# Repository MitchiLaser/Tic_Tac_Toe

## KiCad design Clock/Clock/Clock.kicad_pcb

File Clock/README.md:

# Clock
Ein einfacher Workshop bei dem Kinder eine binäre uhr löten und programmieren können

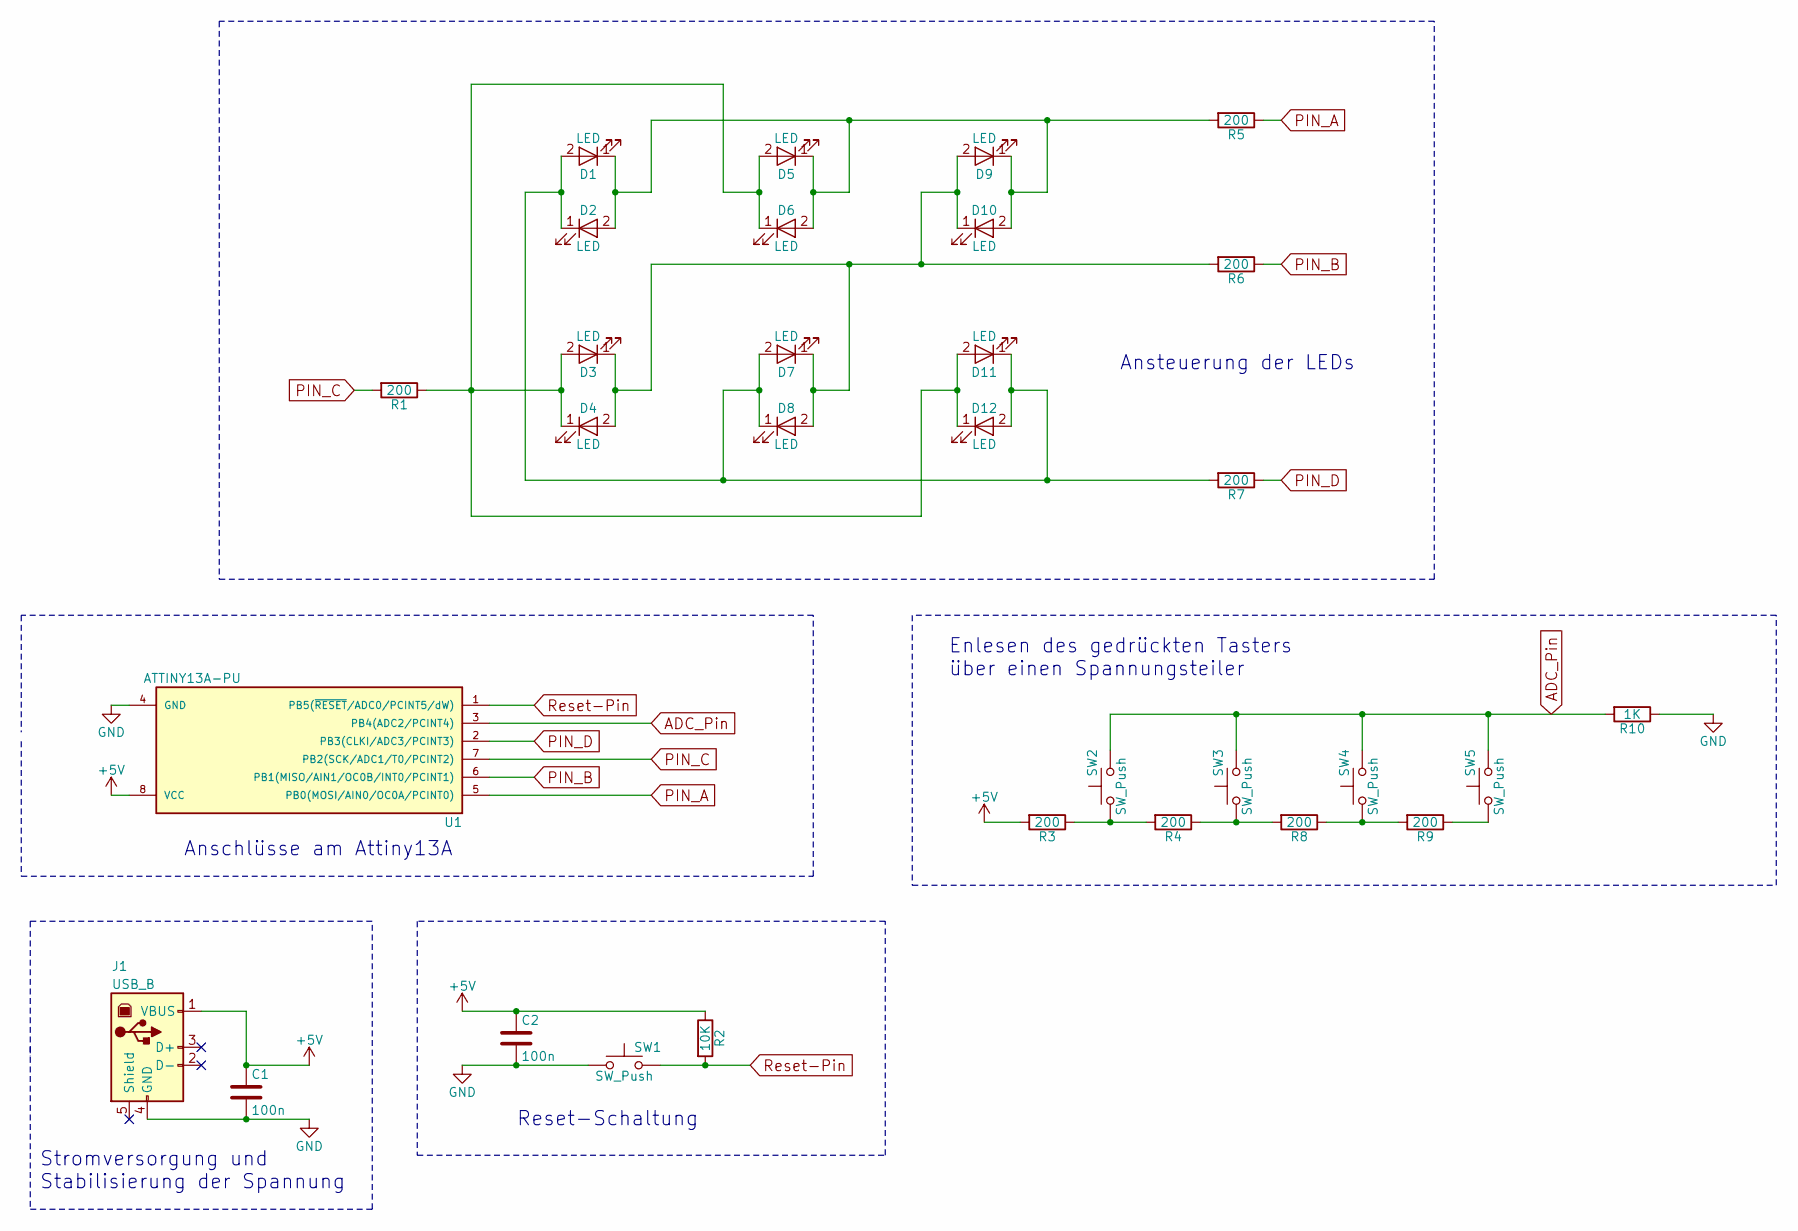
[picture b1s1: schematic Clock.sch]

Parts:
C1, C2: 100n; CP_Radial_Tantal_D5.0mm_P5.00mm
D1, D2, D3, D4, D5, D6, D7, D8, D9, D10, D11, D12: LED; LED_D5.0mm
J1: USB_B
R1, R3, R4, R5, R6, R7, R8, R9: 200; R_Axial_DIN0207_L6.3mm_D2.5mm_P10.16mm_Horizontal
R2: 10K; R_Axial_DIN0207_L6.3mm_D2.5mm_P10.16mm_Horizontal
R10: 1K; R_Axial_DIN0207_L6.3mm_D2.5mm_P10.16mm_Horizontal
SW1, SW2, SW3, SW4, SW5: SW_Push; SW_PUSH_6mm
U1: ATTINY13A-PU; DIP-8_W7.62mm

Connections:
+5V: C1.1, C2.1, J1.1 (VBUS), R2.1, R3.2, U1.8 (VCC)
ADC_Pin: R10.2, SW2.2, SW3.2, SW4.2, SW5.2, U1.3 (PB4(ADC2/PCINT4))
GND: C1.2, C2.2, J1.4 (GND), R10.1, SW1.1, U1.4 (GND)
unnamed: D1.1 (K), D2.2 (A), D5.1 (K), D6.2 (A), D9.1 (K), D10.2 (A), R5.2
unnamed: D1.2 (A), D2.1 (K), D7.2 (A), D8.1 (K), D11.1 (K), D12.2 (A), R7.2
unnamed: D3.1 (K), D4.2 (A), D7.1 (K), D8.2 (A), D9.2 (A), D10.1 (K), R6.2
unnamed: D3.2 (A), D4.1 (K), D5.2 (A), D6.1 (K), D11.2 (A), D12.1 (K), R1.1
unnamed: R3.1, R4.2, SW2.1
unnamed: R4.1, R8.2, SW3.1
unnamed: R8.1, R9.2, SW4.1
unnamed: R9.1, SW5.1
PIN_A: R5.1, U1.5 (PB0(MOSI/AIN0/OC0A/PCINT0))
PIN_B: R6.1, U1.6 (PB1(MISO/AIN1/OC0B/INT0/PCINT1))
PIN_C: R1.2, U1.7 (PB2(SCK/ADC1/T0/PCINT2))
PIN_D: R7.1, U1.2 (PB3(CLKI/ADC3/PCINT3))
Reset-Pin: R2.2, SW1.2, U1.1 (PB5(~RESET~/ADC0/PCINT5/dW))

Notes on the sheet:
Enlesen des gedrückten Tasters über einen Spannungsteiler
Ansteuerung der LEDs
Anschlüsse am Attiny13A
Stromversorgung und Stabilisierung der Spannung
Reset-Schaltung

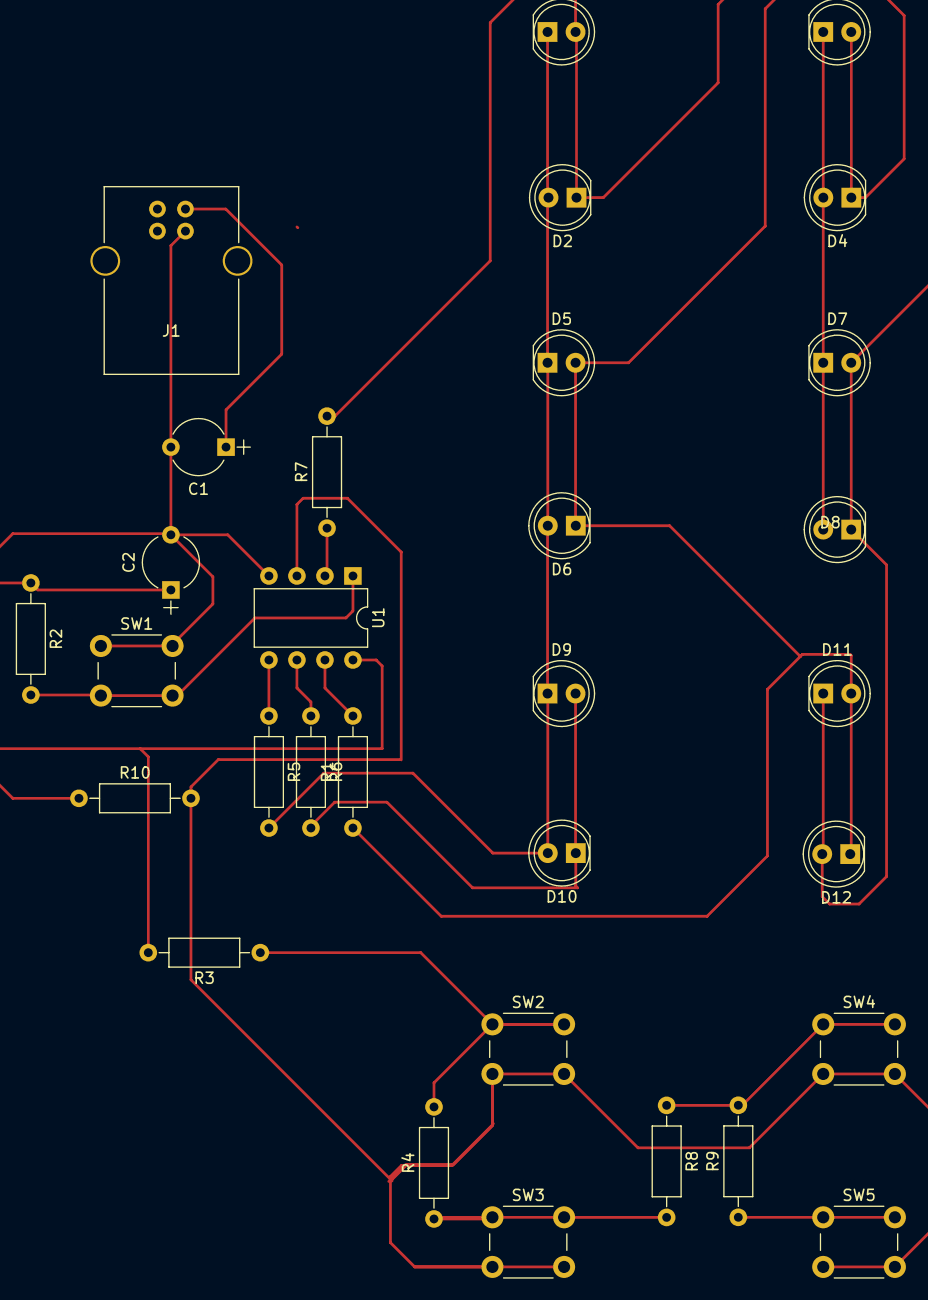
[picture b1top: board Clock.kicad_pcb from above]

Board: 2 copper layers, 31 parts (0 on the bottom side), 16 nets.

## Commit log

2017-09-30 Add Platinenlayout
2017-09-30 Add PlatinenTestcode
2017-09-30 Layout of the platine
2017-10-01 An Platine angepasst
2017-10-01 Kommentare Hinzugefügt
2017-10-03 Create Platine
2017-10-05 Pins richtig eingestellt
2018-11-02 anfang mit Aufräumen
2018-11-02 Dublikate entfernt
2018-11-02 Zusammeführen mehrerer Repos
2018-11-10 Skript zum Tic-Tac-Toe Workshop hinzugefügt
